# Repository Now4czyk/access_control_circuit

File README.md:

# access_control_circuit
Access control circuit

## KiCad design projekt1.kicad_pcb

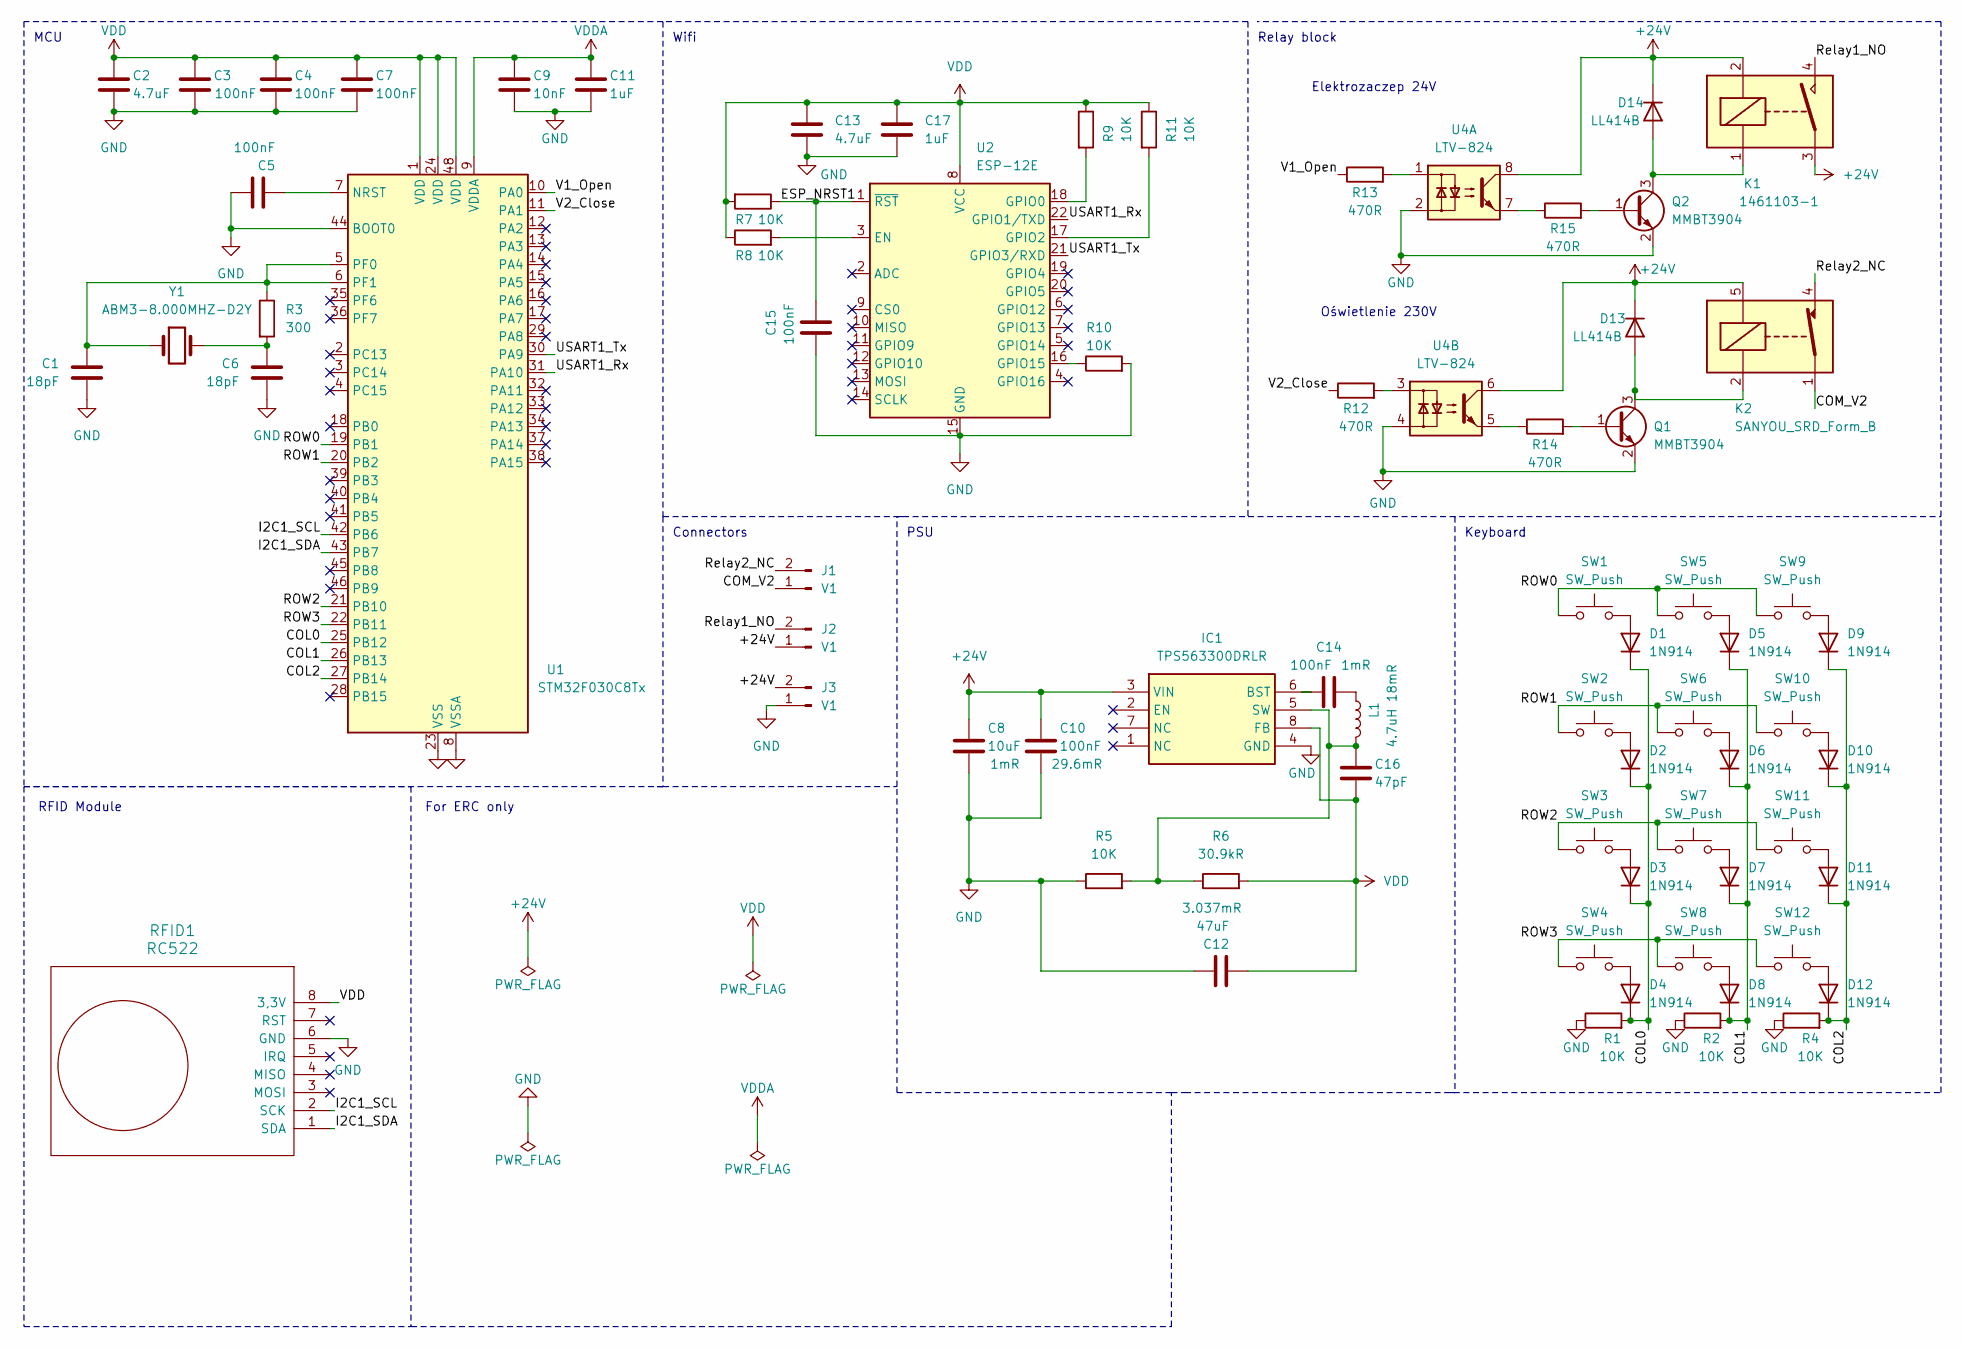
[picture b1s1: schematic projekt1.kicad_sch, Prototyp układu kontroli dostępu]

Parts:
C1, C6: 18pF; C_0603_1608Metric_Pad1.08x0.95mm_HandSolder
C2, C13: 4.7uF; C_0603_1608Metric_Pad1.08x0.95mm_HandSolder
C3, C4, C5, C7, C10, C14, C15: 100nF; C_0603_1608Metric_Pad1.08x0.95mm_HandSolder
C8: 10uF; C_0603_1608Metric_Pad1.08x0.95mm_HandSolder
C9: 10nF; C_0603_1608Metric_Pad1.08x0.95mm_HandSolder
C11, C17: 1uF; C_0603_1608Metric_Pad1.08x0.95mm_HandSolder
C12: 47uF; C_0603_1608Metric_Pad1.08x0.95mm_HandSolder
C16: 47pF; C_0603_1608Metric_Pad1.08x0.95mm_HandSolder
D1, D2, D3, D4, D5, D6, D7, D8, D9, D10, D11, D12: 1N914; D_DO-35_SOD27_P7.62mm_Horizontal
D13, D14: LL414B; D_SOD-523
IC1: TPS563300DRLR; SOTFL50P160X60-8N; Mouser Part Number 595-TPS563300DRLR
J1: V1; TerminalBlock_Altech_AK300-2_P5.00mm
J2, J3: V1; TerminalBlock_TE_282834-2_1x02_P2.54mm_Horizontal
K1: 1461103-1; Relay1461103-1
K2: SANYOU_SRD_Form_B; Relay_SPST_SANYOU_SRD_Series_Form_B
L1: 4.7uH; L_0603_1608Metric_Pad1.05x0.95mm_HandSolder
Q1, Q2: MMBT3904; SOT-23
R1, R2, R4, R5, R7, R8, R9, R10, R11: 10K; R_0603_1608Metric_Pad0.98x0.95mm_HandSolder
R3: 300; R_0603_1608Metric
R6: 30.9kR; R_0603_1608Metric_Pad0.98x0.95mm_HandSolder
R12, R13, R14, R15: 470R; R_0603_1608Metric_Pad0.98x0.95mm_HandSolder
RFID1: RC522; RC522_I2C_B30x20mm
SW1, SW2, SW3, SW4, SW5, SW6, SW7, SW8, SW9, SW10, SW11, SW12: SW_Push; SW_DIP_SPSTx01_Slide_Copal_CHS-01A_W5.08mm_P1.27mm_JPin
U1: STM32F030C8Tx; LQFP-48_7x7mm_P0.5mm
U2: ESP-12E
U4: LTV-824; DIP-8_W7.62mm
Y1: ABM3-8.000MHZ-D2Y; Crystal_SMD_Abracon_ABM3-2Pin_5.0x3.2mm_HandSoldering

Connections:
+24V: C8.1, C10.1, D13.1 (K), D14.1 (K), IC1.3 (VIN), J2.1, J3.2, K1.2, K1.3, K2.5, U4.6, U4.8
/COL0: D1.1 (K), D2.1 (K), D3.1 (K), D4.1 (K), R1.2, U1.25 (PB12)
/COL1: D5.1 (K), D6.1 (K), D7.1 (K), D8.1 (K), R2.2, U1.26 (PB13)
/COL2: D9.1 (K), D10.1 (K), D11.1 (K), D12.1 (K), R4.2, U1.27 (PB14)
/COM_V2: J1.1, K2.1
/ESP_NRST1: C15.1, R7.1, U2.1 (~RST)
/I2C1_SCL: RFID1.2 (SCK), U1.42 (PB6)
/I2C1_SDA: RFID1.1 (SDA), U1.43 (PB7)
/ROW0: SW1.1, SW5.1, SW9.1, U1.19 (PB1)
/ROW1: SW2.1, SW6.1, SW10.1, U1.20 (PB2)
/ROW2: SW3.1, SW7.1, SW11.1, U1.21 (PB10)
/ROW3: SW4.1, SW8.1, SW12.1, U1.22 (PB11)
/Relay1_NO: J2.2, K1.4
/Relay2_NC: J1.2, K2.4
/USART1_Rx: U1.31 (PA10), U2.22 (GPIO1/TXD)
/USART1_Tx: U1.30 (PA9), U2.21 (GPIO3/RXD)
/V1_Open: R13.1, U1.10 (PA0)
/V2_Close: R12.1, U1.11 (PA1)
GND: C1.1, C2.2, C3.2, C4.2, C5.2, C6.1, C7.2, C8.2, C9.2, C10.2, C11.2, C12.1, C13.2, C15.2, C17.2, IC1.4 (GND), J3.1, Q1.2 (E), Q2.2 (E), R1.1, R2.1, R4.1, R5.1, R10.2, RFID1.6 (GND), U1.8 (VSSA), U1.23 (VSS), U1.44 (BOOT0), U1.47 (VSS), U2.15 (GND), U4.2, U4.4
unnamed: C6.2, R3.2, Y1.2
unnamed: C14.2, L1.1
unnamed: D1.2 (A), SW1.2
unnamed: D2.2 (A), SW2.2
unnamed: D3.2 (A), SW3.2
unnamed: D4.2 (A), SW4.2
unnamed: D5.2 (A), SW5.2
unnamed: D6.2 (A), SW6.2
unnamed: D7.2 (A), SW7.2
unnamed: D8.2 (A), SW8.2
unnamed: D9.2 (A), SW9.2
unnamed: D10.2 (A), SW10.2
unnamed: D11.2 (A), SW11.2
unnamed: D12.2 (A), SW12.2
unnamed: D13.2 (A), K2.2, Q1.3 (C)
unnamed: D14.2 (A), K1.1, Q2.3 (C)
unnamed: C14.1, IC1.6 (BST)
unnamed: C16.1, IC1.5 (SW), L1.2, R5.2, R6.1
unnamed: Q1.1 (B), R14.2
unnamed: Q2.1 (B), R15.2
unnamed: R12.2, U4.3
unnamed: R13.2, U4.1
unnamed: R14.1, U4.5
unnamed: R15.1, U4.7
unnamed: C5.1, U1.7 (NRST)
unnamed: C1.2, R3.1, U1.5 (PF0), U1.6 (PF1), Y1.1
unnamed: R8.2, U2.3 (EN)
unnamed: R9.2, U2.18 (GPIO0)
unnamed: R11.2, U2.17 (GPIO2)
unnamed: R10.1, U2.16 (GPIO15)
VDD: C2.1, C3.1, C4.1, C7.1, C12.2, C13.1, C16.2, C17.1, IC1.8 (FB), R6.2, R7.2, R8.1, R9.1, R11.1, RFID1.8 (3,3V), U1.1 (VDD), U1.24 (VDD), U1.48 (VDD), U2.8 (VCC)
VDDA: C9.1, C11.1, U1.9 (VDDA)

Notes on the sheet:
Wifi
For ERC only
Keyboard
Elektrozaczep 24V
Connectors
PSU
MCU
Relay block
RFID Module
Oświetlenie 230V

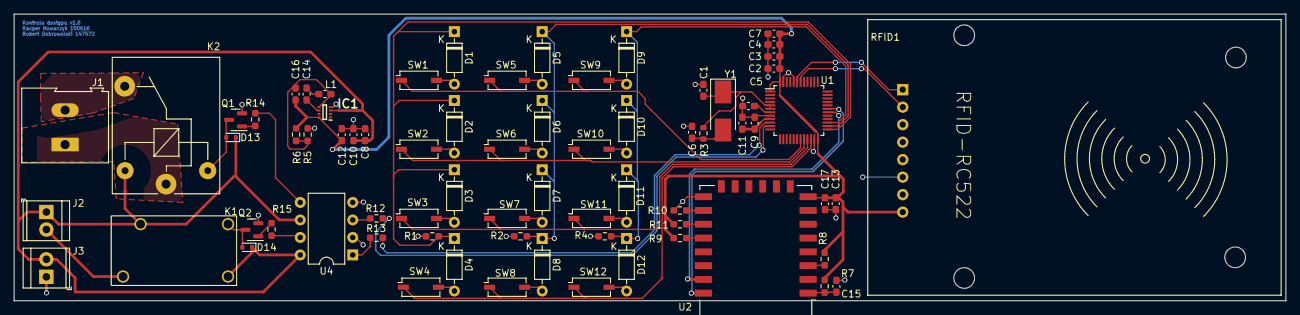
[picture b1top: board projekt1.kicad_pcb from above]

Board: 2 copper layers, 184.6 x 41.6 mm, 72 parts (0 on the bottom side), 51 nets.

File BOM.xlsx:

| Source:
 | Date: | 45262.61388888889
 | Tool: | Eeschema 7.0.8
 | Generator: | C:\Program Files\KiCad\7.0\bin\scripting\plugins/bom_csv_grouped_by_value_with_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
 | Component Count: | 71.0
lp. | Ref | Liczba | Wartość | Nazwa | Footprint | Opis | Dostawca | Koszt j. ( 1szt) | Cena (1 PCB) | Koszt j. ( 10szt) | Cena (10 PCB) | Koszt j. ( 100szt) | Cena (100 PCB) | Link
1.0 | C1, C6 | 2.0 | 18pF | C | "0603" | Unpolarized capacitor | Mouser Electronics | 0.77 | 1.54 | 0.56 | 11.2 | 0.26 | 52 | https://www.mouser.pl/ProductDetail/YAGEO/AC0805JRNPO0BN180?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
2.0 | C2, C13 | 2.0 | 4.7uF | C | "0603" | Unpolarized capacitor | Mouser Electronics | 1.33 | 2.66 | 0.68 | 13.6 | 0.44 | 88 | https://www.mouser.pl/ProductDetail/TDK/C1608X5R1E475K080AC?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
3.0 | C3, C4, C5, C7, C10, C14, C15 | 7.0 | 100nF | C | "0603" | Unpolarized capacitor | Mouser Electronics | 0.43 | 3.01 | 0.15 | 10.5 | 0.09 | 63 | https://www.mouser.pl/ProductDetail/TDK/C1005X7R1C104K050BC?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
4.0 | C8 | 1.0 | 10uF | C | "0603" | Unpolarized capacitor | Mouser Electronics | 3.92 | 3.92 | 2.98 | 29.8 | 2.13 | 213 | https://www.mouser.pl/ProductDetail/KYOCERA-AVX/0805YC106KAT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
5.0 | C9 | 1.0 | 10nF | C | "0603" | Unpolarized capacitor | Mouser Electronics | 0.43 | 0.43 | 0.31 | 3.1 | 0.15 | 15 | https://www.mouser.pl/ProductDetail/KYOCERA-AVX/08051C103J4Z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
6.0 | C11, C17 | 2.0 | 1uF | C | "0603" | Unpolarized capacitor | Mouser Electronics | 0.43 | 0.86 | 0.43 | 8.6 | 0.43 | 86 | https://www.mouser.pl/ProductDetail/KYOCERA-AVX/KGM05AR51A10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
7.0 | C12 | 1.0 | 47uF | C | "0603" | Unpolarized capacitor | Mouser Electronics | 1.72 | 1.72 | 1.22 | 12.2 | 0.81 | 81 | https://www.mouser.pl/ProductDetail/KYOCERA-AVX/CM105X5R476M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
8.0 | C16 | 1.0 | 47pF | C | "0603" | Unpolarized capacitor | Mouser Electronics | 1.22 | 1.22 | 0.75 | 7.5 | 0.42 | 42 | https://www.mouser.pl/ProductDetail/KYOCERA-AVX/0402YA470KAT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
9.0 | D1, D2, D3, D4, D5, D6, D7, D8, D9, D10, D11, D12 | 12.0 | 1N914 | 1N914 | D_DO-35_SOD27 | 100V 0.3A Small Signal Fast Switching Diode, DO-35 | Mouser Electronics | 3.92 | 47.04 | 3.92 | 470.4 | 3.66 | 4392 | https://www.mouser.pl/ProductDetail/Microchip-Technology/1N9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
10.0 | D13, D14 | 2.0 | LL414B | 1N914WT | D_SOD-523 | 75V 0.15A Fast switching Diode, SOD-523 | TME Electronic Components | 0.12768 | 0.25536 | 0.12768 | 2.5536 | 0.125685 | 25.137 | https://www.tme.eu/en/details/1n4148x-tp/smd-universal-diode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
11.0 | IC1 | 1.0 | TPS563300DRLR | TPS563300DRLR | SOTFL50P160X60-8N | TPS563300 3.8-V to 28-V, 3-A Synchronous Buck Converter in SOT583 Package | Mouser Electronics | 2.67 | 2.67 | 2.28 | 22.8 | 1.7 | 170 | https://www.mouser.pl/ProductDetail/Texas-Instruments/TPS563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
12.0 | J1 | 1.0 | V1 | Conn_01x02_Pin | AK300-2_P5.00mm | Generic connector, single row, 01x02, script generated | TME Electronic Components | 2.06 | 2.06 | 1.72 | 17.2 | 1.53 | 153 | https://www.tme.com/in/en/details/tb-5.0-k45-2p/pcb-terminal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
13.0 | J2 | 1.0 | V1 | Conn_01x02_Pin | TE_282834-2_1x02_P2.54mm_Horizontal | Generic connector, single row, 01x02, script generated | TE Connectivity | 6.75 | 6.75 | 6.6 | 66 | 6.1 | 610 | https://www.te.com/usa-en/product-282834-2.html
14.0 | K1 | 1.0 | 1461103-1 | 1461103-1 | Relay1461103-1 |  | Mouser Electronics | 8.66 | 8.66 | 8.2 | 82 | 7.04 | 704 | https://www.mouser.pl/ProductDetail/TE-Connectivity-AMP/1461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
15.0 | K2 | 1.0 | SANYOU_SRD_Form_B | SANYOU_SRD_Form_B | Relay_SPST_SANYOU_SRD_Series_Form_B | Sanyo SRD relay, Single Pole Miniature Power Relay, Opening Contact | Mouser Electronics | 7.41 | 7.41 | 6.95 | 69.5 | 5.56 | 556 | https://www.mouser.pl/ProductDetail/TE-Connectivity/2071556-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
16.0 | L1 | 1.0 | 4.7uH | L | "0603" | Inductor | Mouser Electronics | 0.9 | 0.9 | 0.79 | 7.9 | 0.57 | 57 | https://www.mouser.pl/ProductDetail/TAIYO-YUDEN/LSQNB160808T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
17.0 | Q1, Q2 | 2.0 | MMBT3904 | MMBT3904 | SOT-23 | 0.2A Ic, 40V Vce, Small Signal NPN Transistor, SOT-23 | Mouser Electronics | 0.77 | 1.54 | 0.45 | 9 | 0.33 | 66 | https://www.mouser.pl/ProductDetail/Diotec-Semiconductor/MMB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
18.0 | R1, R2, R4, R5, R7, R8, R9, R10, R11 | 9.0 | 10K | R | "0603" | Resistor | Mouser Electronics | 0.82 | 7.38 | 0.71 | 63.9 | 0.28 | 252 | https://www.mouser.pl/ProductDetail/Panasonic/ERJ-1GJF1002C?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
19.0 | R3 | 1.0 | 300.0 | R | "0603" | Resistor | Mouser Electronics | 1.08 | 1.08 | 0.91 | 9.1 | 0.36 | 36 | https://www.mouser.pl/ProductDetail/ROHM-Semiconductor/ESR03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
20.0 | R6 | 1.0 | 30.9kR | R | "0603" | Resistor | Mouser Electronics | 0.73 | 0.73 | 0.26 | 2.6 | 0.15 | 15 | https://www.mouser.pl/ProductDetail/Panasonic/ERJ-8ENF30R9V?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
21.0 | R12, R13, R14, R15 | 4.0 | 470R | R | "0603" | Resistor | Mouser Electronics | 1.08 | 4.32 | 0.91 | 36.4 | 0.36 | 144 | https://www.mouser.pl/ProductDetail/ROHM-Semiconductor/ESR03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
22.0 | RFID1 | 1.0 | RC522 | RC522 | RC522 module | RC522 Module | abc-rc.pl | 8.8 | 8.8 | 8.8 | 88 | 8.8 | 880 | https://abc-rc.pl/pl/products/modul-czytnika-rfid-rc522-13-5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
23.0 | SW1, SW2, SW3, SW4, SW5, SW6, SW7, SW8, SW9, SW10, SW11, SW12 | 12.0 | SW_Push | SW_Push | SW_DIP_SPSTx0 | Push button switch, generic, two pins | Jameco Electronics | 1.39 | 16.68 | 1.23 | 147.6 | 1.15 | 1380 | https://www.jameco.com/z/TL59AF160Q-JVP-Jameco-ValuePro-Push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
24.0 | U1 | 1.0 | STM32F030C8Tx | STM32F030C8Tx | LQFP-48 | STMicroelectronics Arm Cortex-M0 MCU, 64KB flash, 8KB RAM, 48 MHz, 2.4-3.6V, 39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 | Mouser Electronics | 11.81 | 11.81 | 10.6 | 106 | 8.52 | 852 | https://www.mouser.pl/ProductDetail/STMicroelectronics/STM32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
25.0 | U2 | 1.0 | ESP-12E | ESP-12E | ESP-12E | 802.11 b/g/n Wi-Fi Module | abc-rc.pl | 12.4 | 12.4 | 12.4 | 124 | 12.4 | 1240 | https://abc-rc.pl/pl/products/modul-wifi-esp8266-esp-1-e-esp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
26.0 | U4 | 1.0 | LTV-824 | LTV-824 | DIP-8_W7.62mm | Dual AC/DC Optocoupler, Vce 35V, CTR 20%, DIP8 | Mouser Electronics | 3.4 | 3.4 | 2.21 | 22.1 | 1.44 | 144 | https://www.mouser.pl/ProductDetail/Lite-On/LTV-824?qs=mlaM%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
27.0 | Y1 | 1.0 | ABM3-8.000MHZ-D2Y | Crystal | ABM3-2Pin_5.0x3.2mm | Two pin crystal | Mouser Electronics | 2.72 | 2.72 | 2.35 | 23.5 | 2.14 | 214 | https://www.mouser.pl/ProductDetail/ABRACON/ABM3-8.000MHZ-D2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
 |  |  |  |  |  |  |  |  | 1PCB |  | 10PCB |  | 100PCB
 |  |  |  |  |  |  |  | Łącznie | Dla 1PCB | Łącznie | Dla 1PCB | Łącznie | Dla 1PBC
 |  |  |  |  |  |  | Razem koszt komponentów | 161.96536 | 161.96536 | 1467.0536 | 146.70536 | 12530.137 | 125.30137
 |  |  |  |  |  |  | Produkcja PCB | 27.93 | 5.586 | 39.501 | 3.9501 | 175.959 | 1.75959

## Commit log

2023-11-18 add circuit scheme
2023-11-18 filled all footprints
2023-11-19 PCB design environment setup
2023-11-19 initial pcb elements arrangement
2023-11-25 pcb connections implemented
2023-11-28 changed connector footprint and adjusted paths width
2023-11-29 add external rfid module connectors
2023-11-29 rfid module
2023-11-30 rc522
2023-11-30 rc522 saved pcb
2023-11-30 add text to footprint
2023-12-02 dla patryka kochaniutkiego
2023-12-02 cleanup
2023-12-02 spilled gnd layer
2023-12-02 rm unnecessary
2023-12-04 lecturer remarks fixes
2023-12-04 finishing touches
